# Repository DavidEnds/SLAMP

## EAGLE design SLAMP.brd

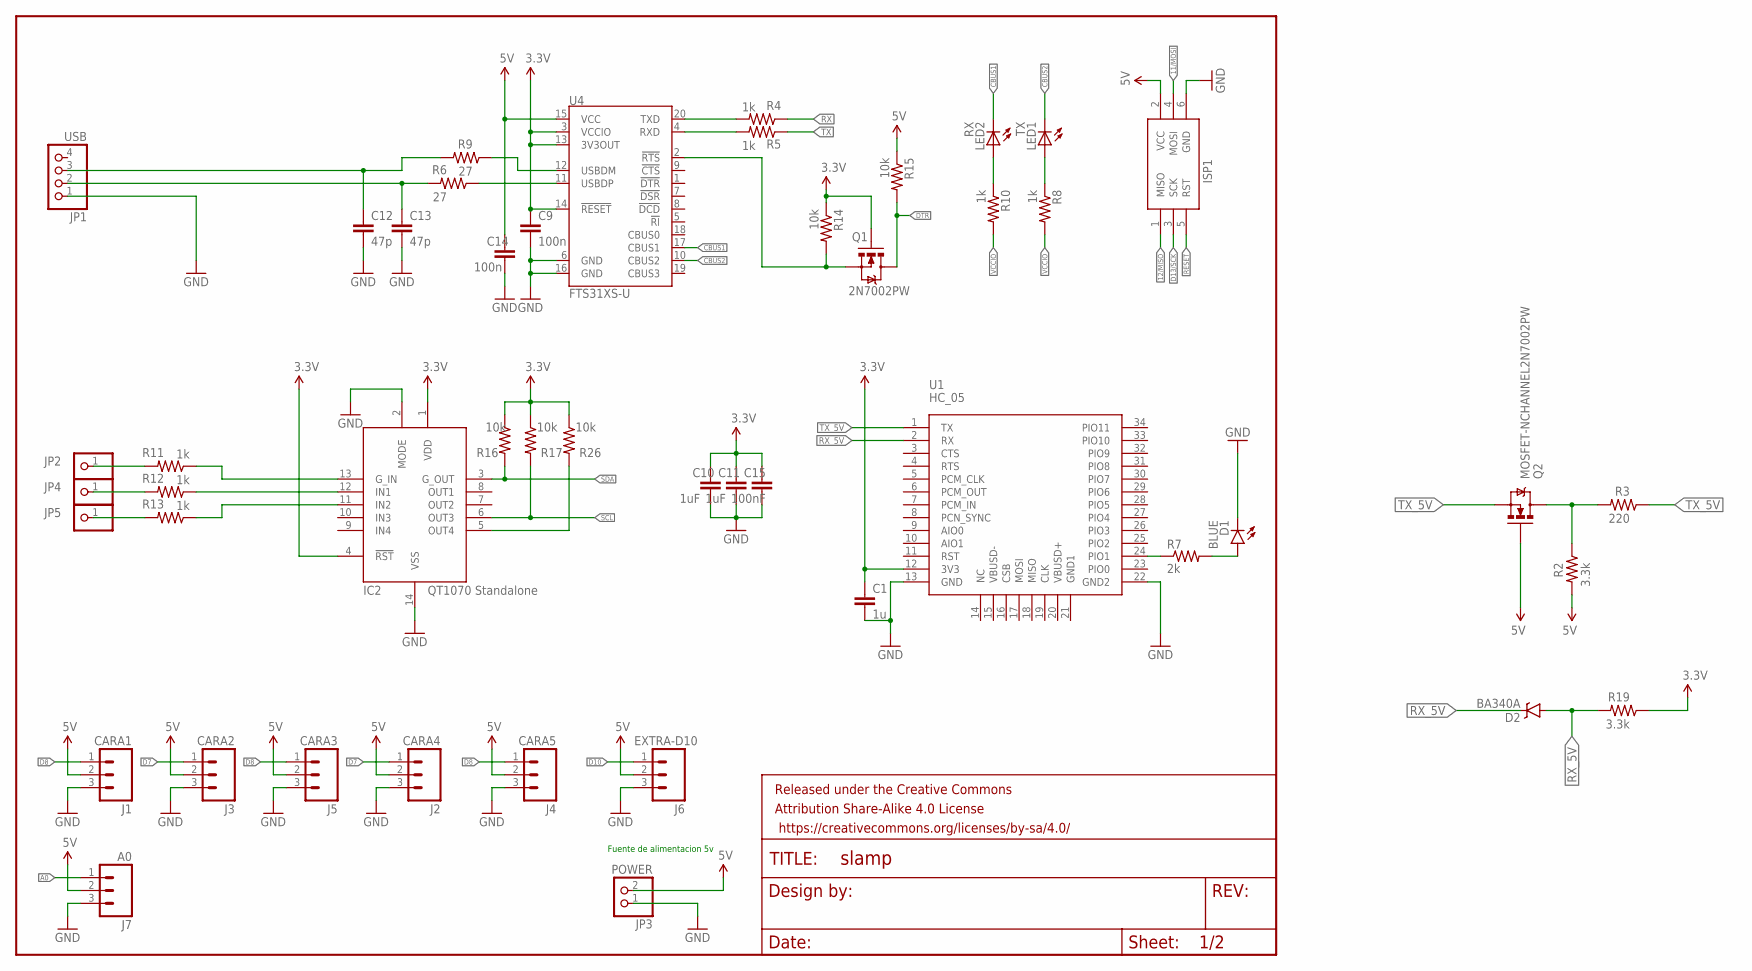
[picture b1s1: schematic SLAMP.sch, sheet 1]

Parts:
C1: 1u; 0603-CAP
C9, C14: 100n; 0603-CAP
C10, C11: 1uF; 0603-CAP
C12, C13: 47p; 0603-CAP
C15: 100nF; 0603-CAP
D1: BLUE; LED-0603
D2: BA340A; SMA-DIODE
FRAME1: FRAME-LETTERNO_PACKAGE; DUMMY
IC2: AT42QT1070-SSU; SO14
ISP1: AVRISP-6; AVRISP
J1: CARA1; JST-3-PTH-VERT
J2: CARA4; JST-3-PTH-VERT
J3: CARA2; JST-3-PTH-VERT
J4: CARA5; JST-3-PTH-VERT
J5: CARA3; JST-3-PTH-VERT
J6: EXTRA-D10; JST-3-PTH-VERT
J7: A0; JST-3-PTH-VERT
JP1: USB; 1X04
JP2, JP4, JP5: PINHD-1X1; 1X01
JP3: POWER; 1X02
LED1: TX; CHIP-LED0603
LED2: RX; CHIP-LED0603
Q1: 2N7002PW; SOT323
Q2: MOSFET-NCHANNEL2N7002PW; SOT323
R2, R19: 3.3k; 0603-RES
R3: 220; 0603-RES
R4, R5: 1k; 0805
R6, R9: 27; 0603-RES
R7: 2k; 0805
R8, R10, R11, R12, R13: 1k; 0603-RES
R14, R15: 10k; 0805
R16, R17, R26: 10k; 0603-RES
U1: HC_05; BLUETOOTH_SMD
U4: FTS31XS-U; SSOP20_L

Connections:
3.3V: C1.1, C9.1, C10.1, C11.1, C15.1, IC2.1 (VDD), IC2.4 (!RST), Q1.1 (G), R14.1, R16.1, R17.1, R19.1, R26.1, U1.12 (3V3), U4.3 (VCCIO), U4.13 (3V3OUT), U4.14 (!RESET); also elsewhere on the board
5V: C14.1, ISP1.2 (VCC), J1.2, J2.2, J3.2, J4.2, J5.2, J6.2, J7.2, JP3.2, Q2.1 (G), R2.2, R15.1, U4.15 (VCC); also elsewhere on the board
11/MOSI: ISP1.4 (MOSI); also elsewhere on the board
12/MISO: ISP1.1 (MISO); also elsewhere on the board
A0: J7.1; also elsewhere on the board
CBUS1: LED2.C, U4.17 (CBUS1)
CBUS2: LED1.C, U4.10 (CBUS2)
D7: J2.1, J3.1; also elsewhere on the board
D8: J1.1, J4.1, J5.1; also elsewhere on the board
D10: J6.1; also elsewhere on the board
D13/SCK: ISP1.3 (SCK); also elsewhere on the board
DTR: Q1.3 (D), R15.2; also elsewhere on the board
GND: C1.2, C9.2, C10.2, C11.2, C12.2, C13.2, C14.2, C15.2, D1.C, IC2.2 (MODE), IC2.14 (VSS), ISP1.6 (GND), J1.3, J2.3, J3.3, J4.3, J5.3, J6.3, J7.3, JP1.1, JP3.1, U1.13 (GND), U1.22 (GND2), U4.6 (GND), U4.16 (GND); also elsewhere on the board
unnamed: R7.1, U1.24 (PIO1)
unnamed: Q1.2 (S), R14.2, U4.2 (!RTS)
unnamed: Q2.3 (D), R2.1, R3.2
unnamed: D1.A, R7.2
unnamed: LED1.A, R8.1
unnamed: LED2.A, R10.1
unnamed: IC2.13 (G_IN), R11.1
unnamed: IC2.12 (IN1), R12.1
unnamed: IC2.11 (IN2), R13.1
unnamed: R6.1, U4.11 (USBDP)
unnamed: R9.1, U4.12 (USBDM)
unnamed: C13.1, JP1.2, R6.2
unnamed: C12.1, JP1.3, R9.2
unnamed: JP2.1, R11.2
unnamed: JP4.1, R12.2
unnamed: JP5.1, R13.2
unnamed: IC2.5 (OUT4), R26.2
RESET: ISP1.5 (RST); also elsewhere on the board
RX: R4.1, R5.2, U4.4 (RXD); also elsewhere on the board
RX_5V: D2.A, D2.C, R19.2, U1.2 (RX); also elsewhere on the board
SCL: IC2.6 (OUT3), R17.2; also elsewhere on the board
SDA: IC2.3 (G_OUT), R16.2; also elsewhere on the board
TX: R4.2, R5.1, U4.20 (TXD); also elsewhere on the board
TX_5V: Q2.2 (S), R3.1, U1.1 (TX); also elsewhere on the board
VCCIO: R8.2, R10.2

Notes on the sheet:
Fuente de alimentacion 5v

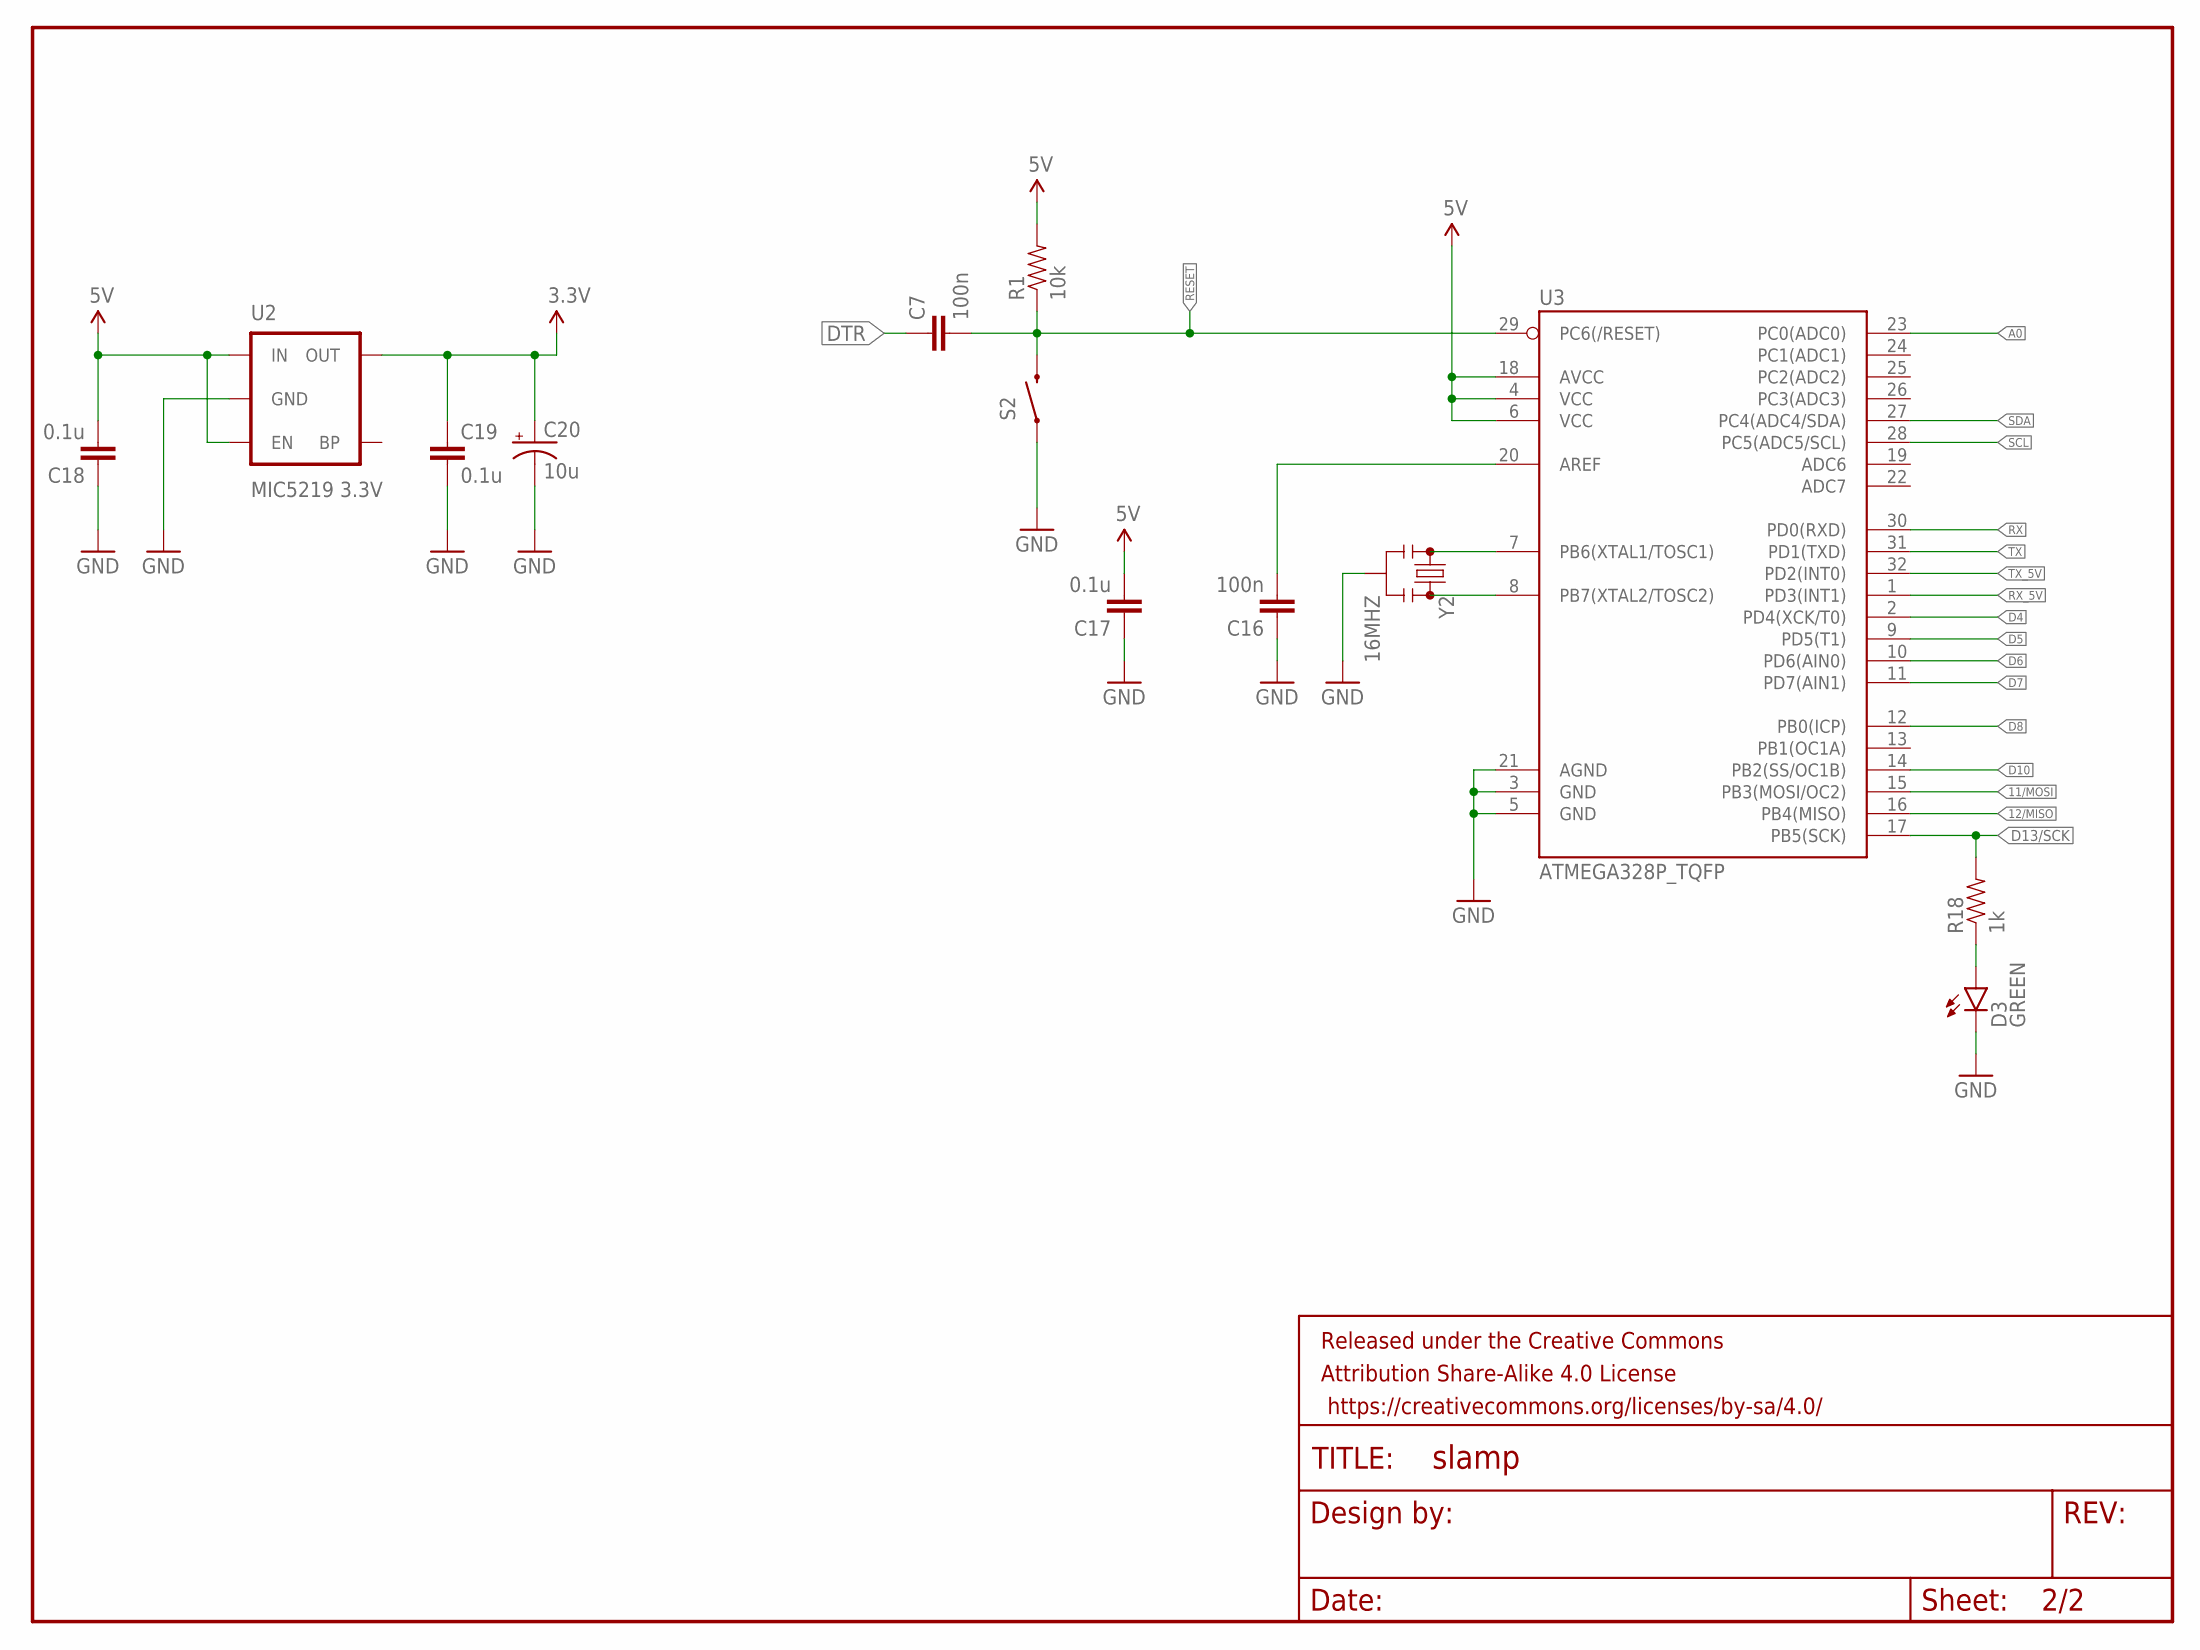
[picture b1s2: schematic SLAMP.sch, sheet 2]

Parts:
C7, C16: 100n; 0805
C17: 0.1u; 0805
C18, C19: 0.1u; 0603-CAP
C20: 10u; SMC_P
D3: GREEN; LED-0603
FRAME2: FRAME-LETTERNO_PACKAGE; DUMMY
R1: 10k; 0805
R18: 1k; 0805
S2: SWITCH-MOMENTARY-2PTH; TACTILE-PTH
U2: MIC5219 3.3V; SOT23-5
U3: ATMEGA328P_TQFP; TQFP32-08
Y2: 16MHZ; RESONATOR-SMD

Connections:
3.3V: C19.1, C20.+, U2.5 (OUT); also elsewhere on the board
5V: C17.2, C18.2, R1.2, U2.1 (IN), U2.3 (EN), U3.4 (VCC), U3.6 (VCC), U3.18 (AVCC); also elsewhere on the board
11/MOSI: U3.15 (PB3(MOSI/OC2)); also elsewhere on the board
12/MISO: U3.16 (PB4(MISO)); also elsewhere on the board
A0: U3.23 (PC0(ADC0)); also elsewhere on the board
D4: U3.2 (PD4(XCK/T0))
D5: U3.9 (PD5(T1))
D6: U3.10 (PD6(AIN0))
D7: U3.11 (PD7(AIN1)); also elsewhere on the board
D8: U3.12 (PB0(ICP)); also elsewhere on the board
D10: U3.14 (PB2(SS/OC1B)); also elsewhere on the board
D13/SCK: R18.2, U3.17 (PB5(SCK)); also elsewhere on the board
DTR: C7.1; also elsewhere on the board
GND: C16.1, C17.1, C18.1, C19.2, C20.-, D3.C, S2.1, U2.2 (GND), U3.3 (GND), U3.5 (GND), U3.21 (AGND), Y2.2; also elsewhere on the board
unnamed: U3.7 (PB6(XTAL1/TOSC1)), Y2.1
unnamed: U3.8 (PB7(XTAL2/TOSC2)), Y2.3
unnamed: C16.2, U3.20 (AREF)
unnamed: D3.A, R18.1
RESET: C7.2, R1.1, S2.3 (2), U3.29 (PC6(/RESET)); also elsewhere on the board
RX: U3.30 (PD0(RXD)); also elsewhere on the board
RX_5V: U3.1 (PD3(INT1)); also elsewhere on the board
SCL: U3.28 (PC5(ADC5/SCL)); also elsewhere on the board
SDA: U3.27 (PC4(ADC4/SDA)); also elsewhere on the board
TX: U3.31 (PD1(TXD)); also elsewhere on the board
TX_5V: U3.32 (PD2(INT0)); also elsewhere on the board

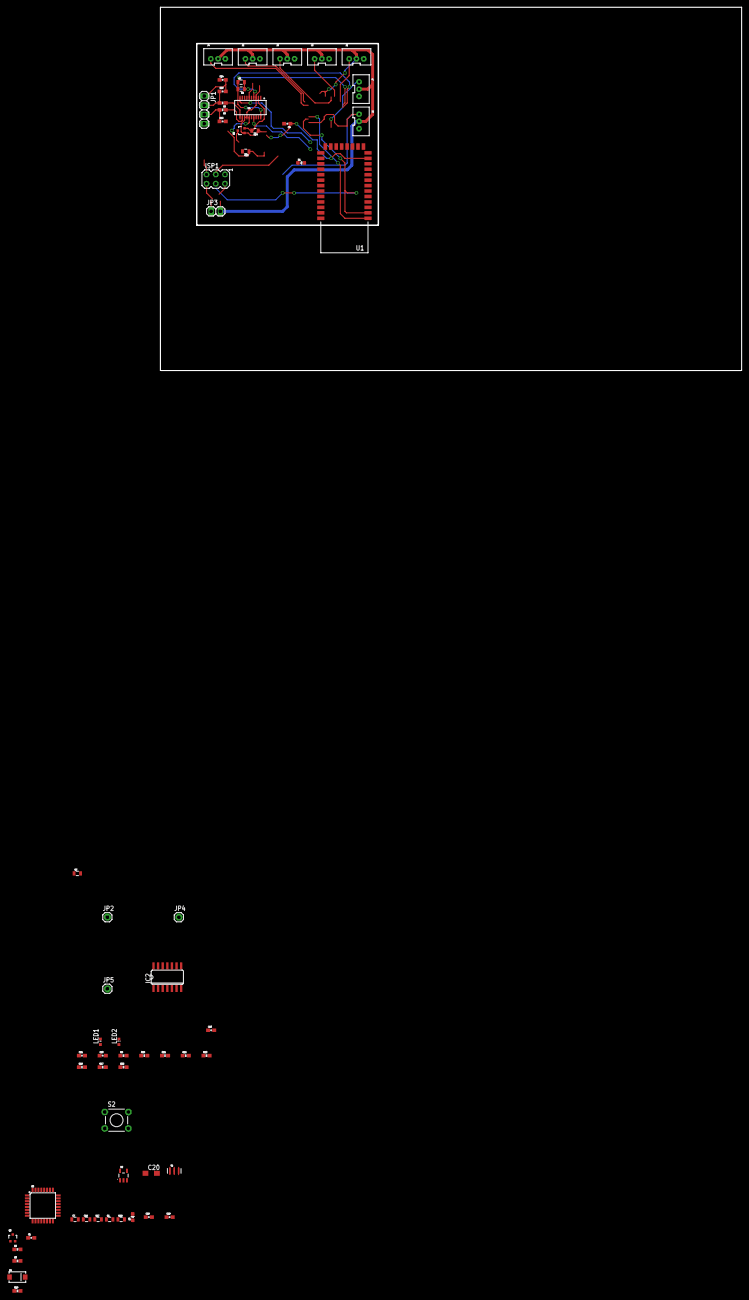
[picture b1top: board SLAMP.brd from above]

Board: 2 copper layers, 160.0 x 100.0 mm, 63 parts (0 on the bottom side), 42 nets.

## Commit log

2016-11-19 Placa empezada
2017-02-26 capacitive touch sensor added
2017-02-26 LM358 added
2017-02-27 Making some changes
2017-02-27 Atmega328p finished
2017-03-05 Improving schematic
2017-03-05 Changing schematic
2017-04-16 adding system for power management
2017-05-13 Working on the power management
2017-05-13 Power control finished

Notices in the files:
parts and their libraries:
SparkFun-Passives: Licensing: Creative Commons ShareAlike 4.0 International - https://creativecommons.org/licenses/by-sa/4.0
SparkFun-Aesthetics: Released under the Creative Commons Attribution Share-Alike 4.0 License
SparkFun-Aesthetics: https://creativecommons.org/licenses/by-sa/4.0
